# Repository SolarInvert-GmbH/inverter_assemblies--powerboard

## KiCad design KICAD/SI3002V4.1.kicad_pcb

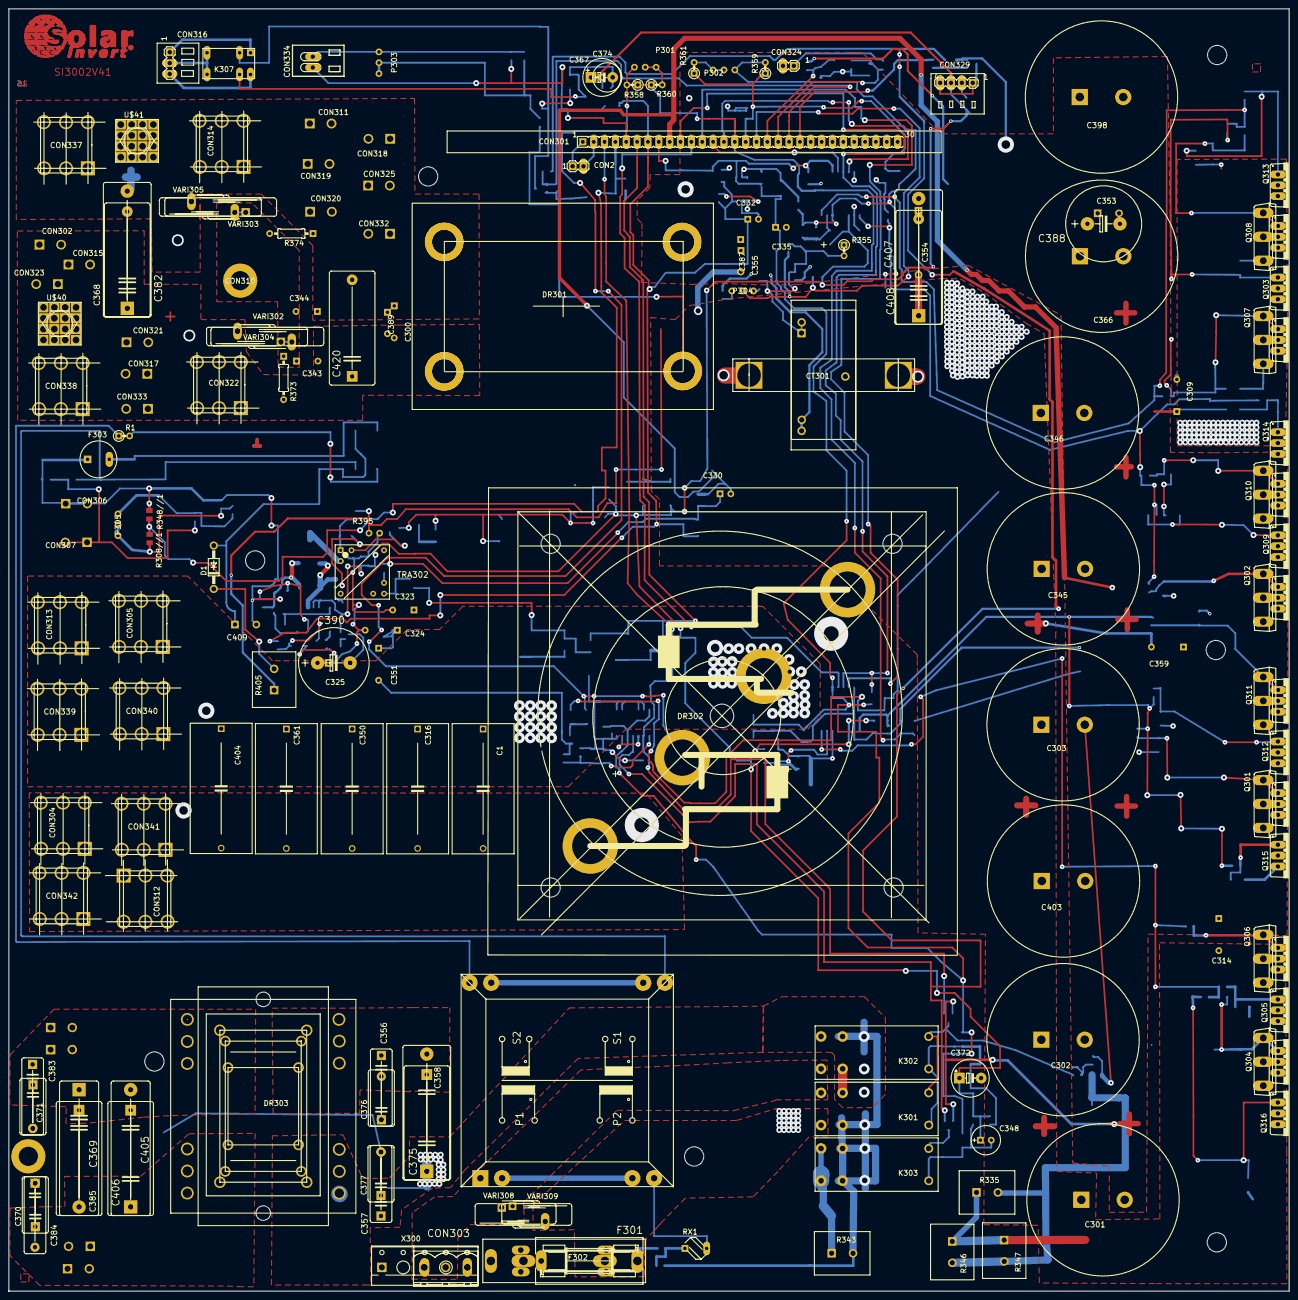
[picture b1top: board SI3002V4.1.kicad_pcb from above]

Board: 16 copper layers, 299.6 x 300.0 mm, 330 parts (0 on the bottom side), 120 nets.

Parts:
@HOLE0, @HOLE1, @HOLE2, @HOLE3, @HOLE4, @HOLE5, @HOLE6: (no value)
B1: DB?GLS20; DBS
C1, C316, C361, C404: 22µF/63V; C-27,5
C300, C355, C359: 100nF/250V; KOND_RM7.5
C301, C302, C303, C345, C346, C366, C398, C403: 5600µF/100V; KOND_D35
C304: 10µ/10V; SMD-C-TANTAL-MITTEL
C305, C306, C308, C311, C312, C315, C342, C349: 100nF/63V; C1206
C307: 2,2µF / 20V Tantal; SMC_B
C309, C314: 10nF/250V; KOND_RM7.5
C310: 10µF/10V; SMD-C-TANTAL-MITTEL
C313: 2,2µF/20V Tantal; SMC_B
C318: 330n/50V; C1206
C319: 330p/50V; C0805
C320: 10n/50V; C0805
C321, C327, C329, C333, C334, C337, C339: 100n/63V; C1206
C322: 1n/50V; C0805
C323: 1nF/100V; KOND_RM5
C324: 100n/250V; KOND_RM7.5
C325, C409: 100µF/160V; ELKO_RM5
C326, C328, C336, C338, C340, C341: 22µ/20V; SMD-C-TANTAL
C330, C332, C335: 100µ/20V; ELKO_RM2.5
C331: 100n/250V; C1206
C343, C344: 100n/200V; KOND_RM5
C348, C367: 100µF/20-25V; E2,5-7
C350: 22µ/63V; C-27,5
C351: 100nF/100V; KOND_RM7.5
C352: 1µF/20V Tantal; SMC_A
C353: 100µF/100V; ELKO_RM5
C354: 1µF/100V; KOND_RM15
C356, C357: 4,7nF Y1; C15B5
C358, C368, C385, C405, C408, C420: 330nF X1; C22.5B10
C360: 47n/63V; C1206
C369, C406: 330nF X1; C27.5B9
C370, C371, C376, C377: 4n7 X1 500VAC; C10B6
C372: 220µF/25V; E5-8,5
C374: 100µF/20-25V; E5-8,5
C375: 330nF X1; C27.5B11
C378, C379: 100nF/50V; C1206
C380, C381: ???; C0805
C382, C407: 680nF X1; C27.5B11
C383, C384: 4,7nF X1; C15B5
C386: unbest.; C0805
C387, C389: 100nF/250V; KOND_RM5
C388: 100uF/160V; E7,5-18
C390: C390; E7,5-16
C391: 10n/200V X7R; C1206
C392, C396, C397, C419: C-EUC2220K; C2220K
C399, C400, C401, C402: C-EUC1210; C1210
CON2, CON324: 2pol.Stiftl.; MA02-1
CON301: µC-Platine; FE20
CON302, CON311, CON315, CON317, CON318, CON319, CON323, CON325, CON332, CON333: Steckzunge breit; KONTAKT_GROß
CON303: MSTB03; MSTB-03
CON304, CON305, CON312, CON313, CON314, CON322, CON337, CON338, CON339, CON340, CON341, CON342: POWERCLAMP2; POWERCLAMP
CON306, CON307: Steckzunge klein; KONTAKT_KLEIN
CON308, CON309, CON335, CON336: Steckzunge breit; KONTAKT_KLEIN
CON310, CON330: PE-BOHRUNG; PE-KONTAKT-BOHRUNG
CON316: 3pol.Stiftl.; MA03-1
CON320, CON321: Steckzunge; KONTAKT_GROß
CON329: 4pol.Stiftl.; MA04-1
CON334: PTSA
CT301: AC1050; STROMWANDLER2
D1: 1N4004; DO41-10
D300, D302, D305, D307, D321: BZV55C18V; SMD-DIODE_STANDARD
D301, D303, D306, D308, D325, D326: BAV103; SMD-DIODE_STANDARD
D309, D310, D336, D340, D341: LL4148; SMD-DIODE_STANDARD
D311, D320: BAT46 TMMBAT46; SMD-DIODE_STANDARD
D313: BAS70; SOT23
D314, D315: BAT64; SOT23
D318, D319, D322, D323, D324, D327, D331, D332, D333, D334, D337: BZV55C18; SMD-DIODE_STANDARD
D328, D329: BZV55C4V7; SMD-DIODE_STANDARD
D330: BZV55C5V6; SMD-DIODE_STANDARD
D335: BZV55C18; SMD-DIODE_STANDARD@1
DR301: ???; DC_COIL3
DR302: SINUSDROSSEL3
DR303: 2,7mH/8A; NETZDROSSEL3
F301: ???; SH22,5A
F302: SICHERUNGSHALTER
F303: Bürklin 50G362; TR5
IC301, IC302: IR2110S; SO-16L
IC305: UC2843D; SO-14
IC307: 4093; SO14
K301, K302, K303: RT444012; RT2N_O
K307: G5V1
L300, L302: 22µH/145mA; C1210
L301: 22µH, 260mA; C1812
P301, P302, P303, P304: 22k; POTI2
P305: 100R; POTI2
Q301, Q302, Q304, Q306, Q307, Q308, Q310, Q311: FDP2532; TO247_220
Q303, Q305, Q309, Q312, Q313, Q314, Q315, Q316: FDP2532; TO220BV
R1: 5R1 / 0,6W; 0207_2V
R300, R304, R305, R327, R328, R329, R330, R350, R351, R352, R362, R391, R392, R393, R394: 22; R0805
R301: 22R; R0805
R302, R306, R312, R320, R363: 100k; R0805
R308, R308//1: 1.5k; R0805
R309, R316, R332, R354, R366, R369: 100k; R0805W
R310: 5K1 Typ 503 1% 0,125W; R0805
R313: 51k; R0805
R314: 330k; R0805
R315: 27k; R0805
R317: 2,7k; R0805
R319: 5R6; MINI_MELF-0204W
R333, R337, R368, R370: 10k; R0805
R334: 110k; R0805
R335: 2k2 / 5W; R_LEISTUNG_RM5
R336, R341, R372: 1M; R0805
R338, R339, R342: 120k; R0805
R340, R404: 1k; R0805
R343: 330R/5W; R_LEISTUNG_RM5
R346, R347, R405: 1k5/5W; R_LEISTUNG_RM5
R348, R348//1: je nach Trafo; R0805
R353: 1k2 / 0,25W; R1206
R355: 47R / 0,6W; 0207_2V
R356: 22K; R0805
R357: 22K; M0805
R358, R359, R360, R361: 33K / 0,6W; 0207_2V
R364: 1M; R0805W
R365, R367: 10K; R0805W
R371, R375, R382, R383: 10K; R0805
R373, R374: 100k; 0207_10
R376, R377, R378, R396, R397: 0R; R0805
R379: 10R; R0805
R380: 39R; R0805
R381: 270R; R0805
R384: 100R; R0805
R395: 10R; R_RM2.5
R403: 27K; R0805
RX1: Bü 82 E 3562; B57164
T301, T304, T305, T311: BSS123; SOT23
T306: IRFL214; D2PACK
T307: IRFL214; SOT223R_INFINEON
T312: IRFL214; TRANS_5.5X9
TRA300: RINGKERN
TRA302: HFTRRM5; TRA-RM5
U301: MIC5201-5,0BM; SO-8
U$40, U$41: CONWUERTH_7461097
VARI302, VARI303: S25K130E4R12; S25K40
VARI304, VARI305: S25K130E4R12; S20K40
VARI308: S20K275
VARI309: S20K275; S10K300
X300: W237-146

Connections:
+5V: C304.+, C305.2, C310.+, C311.2, C334.2, C335.+, C349.2, C360.1, CON301.8, D311.+1, D320.+1, IC301.11, IC302.11, IC307.5, IC307.14, U301.1
+7,5V: C332.+, C333.2, CON301.7, D340.+1, L301.2, R312.2, R376.2, U301.8
+15V: C308.2, C315.2, C321.2, C328.+, C329.2, C341.+, C348.+, C367.+, C372.+, C374.+, CON329.3, D301.+1, D306.+1, D335.-2, IC301.3, IC302.3, IC305.11, IC305.12, L300.2, R310.2, R316.1, R333.2, R353.2, R354.1, R368.2
-7,5V: C338.-, C339.1, CON301.6, L302.2
/ANA: C379.1, CON301.19, R366.1, R367.2
/ANALOG: CON324.1, R366.2
/DBRÜCKE1: C306.1, C307.-, D300.+1, D303.-2, D321.+1, D325.+1, D334.+1, D337.+1, DR302.4, IC301.6, P301.U, Q301.D, Q301.D1, Q304.S, Q304.S1, Q305.S, Q306.S, Q306.S1, Q311.D, Q311.D1, Q312.D, Q315.D, Q316.S, R338.2, R358.2
/DBRÜCKE2: C312.1, C313.-, CT301.S2, D305.+1, D308.-2, D318.+1, D323.+1, D326.+1, D332.+1, IC302.6, P302.U, Q302.D, Q302.D1, Q303.S, Q307.S, Q307.S1, Q308.S, Q308.S1, Q309.D, Q310.D, Q310.D1, Q313.S, Q314.D, R339.2, R359.2
/EXT.REL: CON301.20, R369.2, R375.1, T304.L
/L1: CON303.3, F301.2, F302.P$3, F302.P$4, F302.P$7, F302.P$8, X300.3
/LED2: CON301.21, R371.1
/N1: CON303.1, CON303.2, K301.14, K302.24, TRA300.1, VARI308.1, VARI309.1, X300.2
/N$31: CON307.1, CON307.2, R384.1, R403.1, R404.1
/OVER: C378.1, CON301.18, R364.1, R365.2
/PE1: C356.2, C357.2, C370.2, C371.2, C376.1, C377.2, C383.2, C384.1, CON330.0
/RDSON_M1: C381.1, CON301.15, D303.+1, D328.-2, R358.1, R360.1
/RDSON_M2: C380.1, CON301.16, D308.+1, D329.-2, R359.1, R361.1
/REL: CON301.3, IC307.2, R309.2, T305.L
/RT/CT: C319.2, IC305.7, R315.1, R320.1
/SD: C360.2, CON301.10, IC301.13, IC302.13
/T301-ANS: CON301.11, IC301.12
/T302-ANS: CON301.12, IC301.14
/T303-ANS: CON301.13, IC302.12
/T304-ANS: CON301.14, IC302.14
/TRA_L: C369.1, C371.1, C383.1, C385.1, C405.1, C406.2, CON308.1, CON308.2, CON335.1, CON335.2, DR303.P$2, DR303.P$6, DR303.P$10, DR303.P$11, DR303.P$14, DR303.P$18, DR303.P$19
/TRA_N: C369.2, C370.1, C384.2, C385.2, C405.2, C406.1, CON309.1, CON309.2, CON336.1, CON336.2, DR303.P$4, DR303.P$8, DR303.P$12, DR303.P$15, DR303.P$20, DR303.P$21
/UN: C342.2, CON301.4, R308.1, R308//1.1, R348.2, R348//1.2
GND: C301.-, C302.-, C303.-, C304.-, C305.1, C308.1, C309.1, C310.-, C311.1, C314.1, C315.1, C319.1, C320.1, C321.1, C322.1, C323.1, C324.1, C325.-, C326.-, C327.1, C328.-, C329.1, C330.-, C331.1, C332.-, C333.1, C334.1, C335.-, C336.+, C337.2, C338.+, C339.2, C340.-, C341.-, C342.1, C345.-, C346.-, C349.1, C351.1, C352.-, C353.-, C354.1, C355.1, C359.1, C366.-, C378.2, C379.2, C380.2, C381.2, C386.2, C387.1, C388.-, C390.-, C391.1, C398.-, C403.-, C407.2, C408.2, C409.-, CON301.9, CON306.1, CON306.2, CON324.2, CT301.3, CT301.P$2, D302.+1, D307.+1, D319.+1, D322.+1, D324.+1, D327.+1, D328.+1, D329.+1, D330.+1, D331.+1, D333.+1, D335.+1, DR301.1B, DR301.11B, F303.1, IC301.2, IC301.15, IC302.2, IC302.15, IC305.8, IC305.9, IC307.7, IC307.8, IC307.9, IC307.12, IC307.13, Q301.S, Q301.S1, Q302.S, Q302.S1, Q309.S, Q310.S, Q310.S1, Q311.S, Q311.S1, Q312.S, Q314.S, Q315.S, R302.1, R306.1, R309.1, R313.1, R319.1, R332.1, R336.1, R338.1, R339.1, R342.1, R348.1, R348//1.1, R355.1, R357.2, R363.1, R365.1, R367.1, R369.1, R372.1, R381.2, R383.2, R404.2, T301.R, T304.R, T305.R, T311.R, T312.S, TRA302.3, U301.2, U301.3, U301.6, U301.7
unnamed: B1.+, C409.+, D1.A
unnamed: B1.-, F303.2
unnamed: B1.AC1, R403.2, TRA300.5
unnamed: B1.AC2, R1.2
unnamed: C1.1, C316.1, C350.1, C361.1, C392.2, C396.2, C397.2, C399.2, C400.2, C401.2, C402.2, C404.1, C419.2, CON305.1, CON305.2, CON305.3, CON305.4, CON305.5, CON305.6, CON313.1, CON313.2, CON313.3, CON313.4, CON313.5, CON313.6, CON339.1, CON339.2, CON339.3, CON339.4, CON339.5, CON339.6, CON340.1, CON340.2, CON340.3, CON340.4, CON340.5, CON340.6, DR302.2
unnamed: C1.2, C316.2, C350.2, C361.2, C392.1, C396.1, C397.1, C399.1, C400.1, C401.1, C402.1, C404.2, C419.1, CON304.1, CON304.2, CON304.3, CON304.4, CON304.5, CON304.6, CON312.1, CON312.2, CON312.3, CON312.4, CON312.5, CON312.6, CON341.1, CON341.2, CON341.3, CON341.4, CON341.5, CON341.6, CON342.1, CON342.2, CON342.3, CON342.4, CON342.5, CON342.6, DR302.33
unnamed: C300.1, C344.1, C368.2, C382.2, C389.1, C420.2, CON311.1, CON311.2, CON314.1, CON314.2, CON314.3, CON314.4, CON314.5, CON314.6, CON318.1, CON318.2, CON319.1, CON319.2, CON320.1, CON320.2, CON325.1, CON325.2, CON332.1, CON332.2, CON337.1, CON337.2, CON337.3, CON337.4, CON337.5, CON337.6, DR301.1A, DR301.11A, R374.1, U$41.P$1, U$41.P$2, U$41.P$3, U$41.P$4, U$41.P$5, U$41.P$6, U$41.P$7, U$41.P$8, U$41.P$9, U$41.P$10, U$41.P$11, U$41.P$12, U$41.P$13, U$41.P$14, U$41.P$15, U$41.P$16, VARI303.2, VARI305.1
unnamed: C300.2, C343.2, C368.1, C382.1, C389.2, C420.1, CON302.1, CON302.2, CON315.1, CON315.2, CON317.1, CON317.2, CON321.1, CON321.2, CON322.1, CON322.2, CON322.3, CON322.4, CON322.5, CON322.6, CON323.1, CON323.2, CON333.1, CON333.2, CON338.1, CON338.2, CON338.3, CON338.4, CON338.5, CON338.6, DR301.2A, DR301.22A, R373.2, U$40.P$1, U$40.P$2, U$40.P$3, U$40.P$4, U$40.P$5, U$40.P$6, U$40.P$7, U$40.P$8, U$40.P$9, U$40.P$10, U$40.P$11, U$40.P$12, U$40.P$13, U$40.P$14, U$40.P$15, U$40.P$16, VARI302.1, VARI304.2
unnamed: C301.+, C302.+, C303.+, C309.2, C314.2, C345.+, C346.+, C353.+, C354.2, C355.2, C359.2, C366.+, C387.2, C388.+, C398.+, C403.+, C407.1, C408.1, DR301.2B, DR301.22B, Q303.D, Q304.D, Q304.D1, Q305.D, Q306.D, Q306.D1, Q307.D, Q307.D1, Q308.D, Q308.D1, Q313.D, Q316.D, R334.2, R335.1, R346.1, R347.1, R364.2, R379.2, R395.P$2, R405.1
unnamed: C306.2, C307.+, D301.-2, IC301.7
unnamed: C312.2, C313.+, D306.-2, IC302.7
unnamed: C318.1, R314.2
unnamed: C318.2, IC305.3, R312.1, R313.2
unnamed: C320.2, IC305.14, R315.2
unnamed: C322.2, IC305.5, R317.1
unnamed: C323.2, C324.2, C325.+, C390.+, C391.2, R316.2, R354.2, R379.1, R395.P$1, TRA302.1
unnamed: C326.+, C327.2, C340.+, D313.M, L300.1
unnamed: C330.+, C331.2, D314.M, L301.1
unnamed: C336.-, C337.1, D315.L, L302.1
unnamed: C343.1, C344.2, CON310.0, R373.1, R374.2, VARI302.2, VARI303.1, VARI304.1, VARI305.2
unnamed: C348.-, D309.-2, D320.-2, K303.A2, R333.1
unnamed: C351.2, R340.1, R341.2
unnamed: C352.+, D330.-2, IC307.1, R341.1, R342.2
unnamed: C356.1, C358.1, C375.2, C376.2, DR303.P$1, DR303.P$5, DR303.P$9, DR303.P$16, DR303.P$22, DR303.P$23, K303.14, K303.24, R343.1
unnamed: C357.1, C358.2, C375.1, C377.1, DR303.P$3, DR303.P$7, DR303.P$13, DR303.P$17, DR303.P$24, DR303.P$25, K301.11, K302.21
unnamed: C367.-, C374.-, D336.-2, D341.-2, K307.9, R368.1
unnamed: C372.-, D310.-2, D311.-2, K301.A2, K302.A2, R310.1
unnamed: C386.1, CT301.1, CT301.P$1, R355.2, R356.1, R382.1
unnamed: CON2.1, CON301.1
unnamed: CON2.2, CON301.2
unnamed: CON301.5, CON334.P$2, R378.1
unnamed: CON301.17, P304.M, R356.2, R357.1
unnamed: CON316.1, K307.1
unnamed: CON316.2, K307.5, K307.6
unnamed: CON316.3, K307.10
unnamed: CON329.1, CON329.4, T301.M
unnamed: CON329.2, R353.1
unnamed: CON334.P$1, P303.O, R377.1, R378.2
unnamed: CT301.S1, DR302.11
unnamed: D1.C, R405.2
unnamed: D300.-2, Q305.G, R300.1
unnamed: D302.-2, Q311.G, Q311.G1, R301.1
unnamed: D305.-2, Q307.G, Q307.G1, R304.1
unnamed: D307.-2, Q309.G, R305.1
unnamed: D309.+1, K303.A1, T311.M
unnamed: D310.+1, K301.A1, K302.A1, R337.2, T305.M
unnamed: D313.L, TRA302.6
unnamed: D314.L, TRA302.5
unnamed: D315.M, TRA302.4
unnamed: D318.-2, Q313.G, R391.1
unnamed: D319.-2, Q314.G, R392.1
unnamed: D321.-2, Q306.G, Q306.G1, R327.1
unnamed: D322.-2, Q312.G, R328.1
unnamed: D323.-2, Q308.G, Q308.G1, R329.1
unnamed: D324.-2, Q310.G, Q310.G1, R330.1
unnamed: D325.-2, D326.-2, R340.2
unnamed: D327.-2, Q315.G, R394.1
unnamed: D331.-2, Q301.G, Q301.G1, R362.1
unnamed: D332.-2, Q303.G, R350.1
unnamed: D333.-2, Q302.G, Q302.G1, R351.1
unnamed: D334.-2, Q304.G, Q304.G1, R352.1
unnamed: D336.+1, K307.2, T304.M
unnamed: D337.-2, Q316.G, R393.1
unnamed: D340.-2, D341.+1
unnamed: F301.1, F302.P$1, F302.P$2, F302.P$5, F302.P$6, K301.24, K302.14, R397.1, VARI308.2, VARI309.2
unnamed: IC301.1, R301.2, R302.2, R328.2, R362.2, R394.2
unnamed: IC301.8, R300.2, R327.2, R352.2, R393.2
unnamed: IC302.1, R305.2, R306.2, R330.2, R351.2, R392.2
unnamed: IC302.8, R304.2, R329.2, R350.2, R391.2
unnamed: IC305.1, R314.1
unnamed: IC305.10, R363.2, T306.1, T307.G
unnamed: IC307.3, IC307.6
unnamed: IC307.4, R332.2, R370.1, R375.2, T311.L
unnamed: K301.21, K302.11, K303.11, K303.21, R343.2, R396.1
unnamed: P301.M, P301.O, R360.2
unnamed: P302.M, P302.O, R361.2
unnamed: P303.M, P303.U, R334.1, R377.2
unnamed: P304.O, R382.2
unnamed: P304.U, R383.1
unnamed: P305.M, P305.U, R308.2, R308//1.2, R380.2, R381.1
unnamed: P305.O, R380.1, R384.2
unnamed: R1.1, TRA300.8
unnamed: R317.2, R319.2, R320.2, T306.3, T307.S
unnamed: R335.2, R346.2, R347.2, T312.D
unnamed: R336.2, R337.1, T312.GATE
unnamed: R370.2, R371.2, R372.2, T301.L
unnamed: R376.1, U301.5
unnamed: R396.2, R397.2, RX1.1
unnamed: RX1.2, TRA300.4
unnamed: T306.2, T307.4, TRA302.2
unnamed: TRA300.2, TRA300.3
unnamed: TRA300.6, TRA300.7

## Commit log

2023-05-11 First Upload
